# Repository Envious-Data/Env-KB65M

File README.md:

# Env-KB65M
 A 65% Custom Mechanical utilising the raspberry pi pico.
  
### About
A compact 65% design featuring ISO and ANSI layout support as well as a triple split spacebar. I designed this on a whim so its design can be considered somewhat quirky.

### Firmware
If you need a pre-built QMK firmware for this keyboard you can find it [here](https://raw.githubusercontent.com/Envious-Data/EnvKB-QMK/main/_PREBUILTFIRMWARES/enviousdesign_65m_default.uf2)
and [here](https://raw.githubusercontent.com/Envious-Data/EnvKB-QMK/main/_PREBUILTFIRMWARES/enviousdesign_65m_via.uf2)

### how to flash
- hold BOOTSEL button while plugging in USB
- A USB Drive will show up, drag and drop the UF2 file linked above into the Drive
- Done!

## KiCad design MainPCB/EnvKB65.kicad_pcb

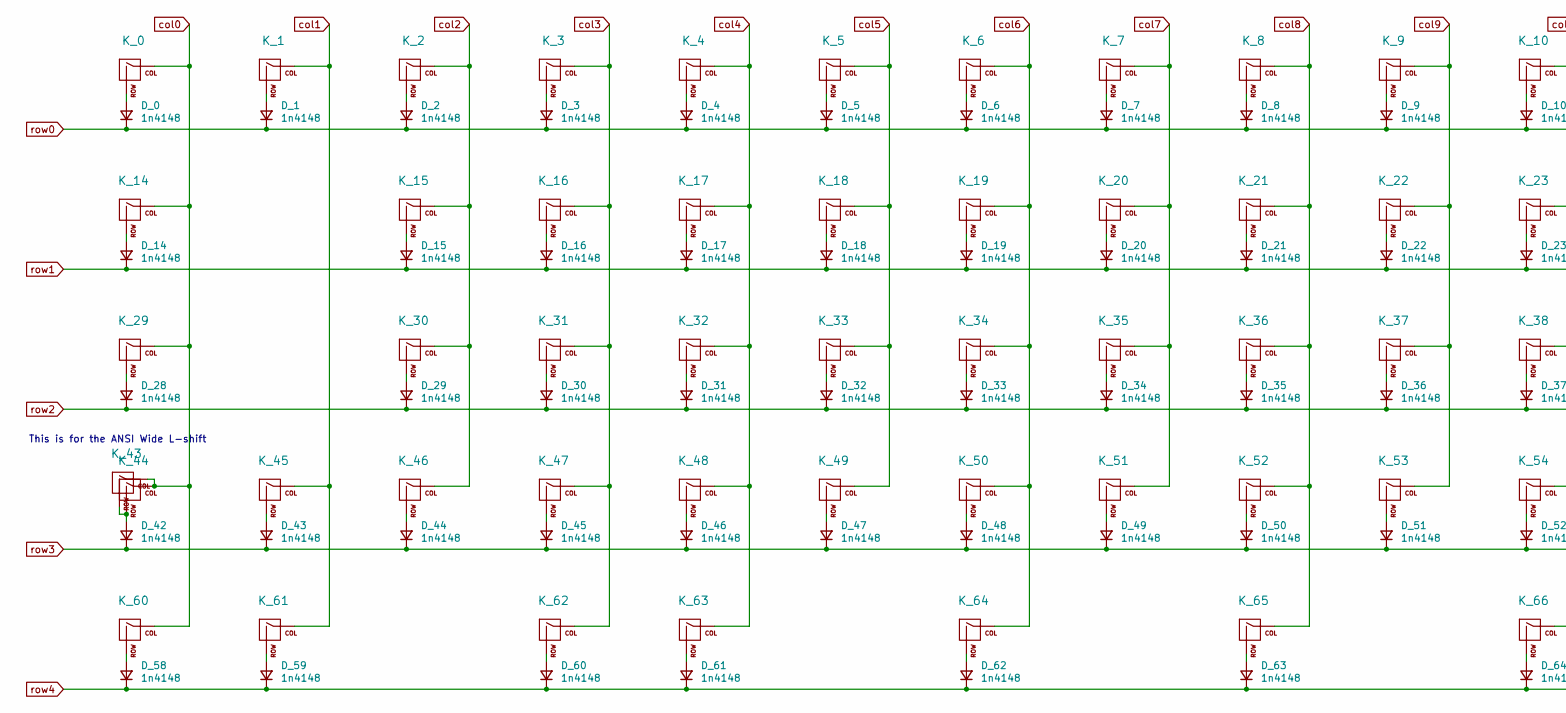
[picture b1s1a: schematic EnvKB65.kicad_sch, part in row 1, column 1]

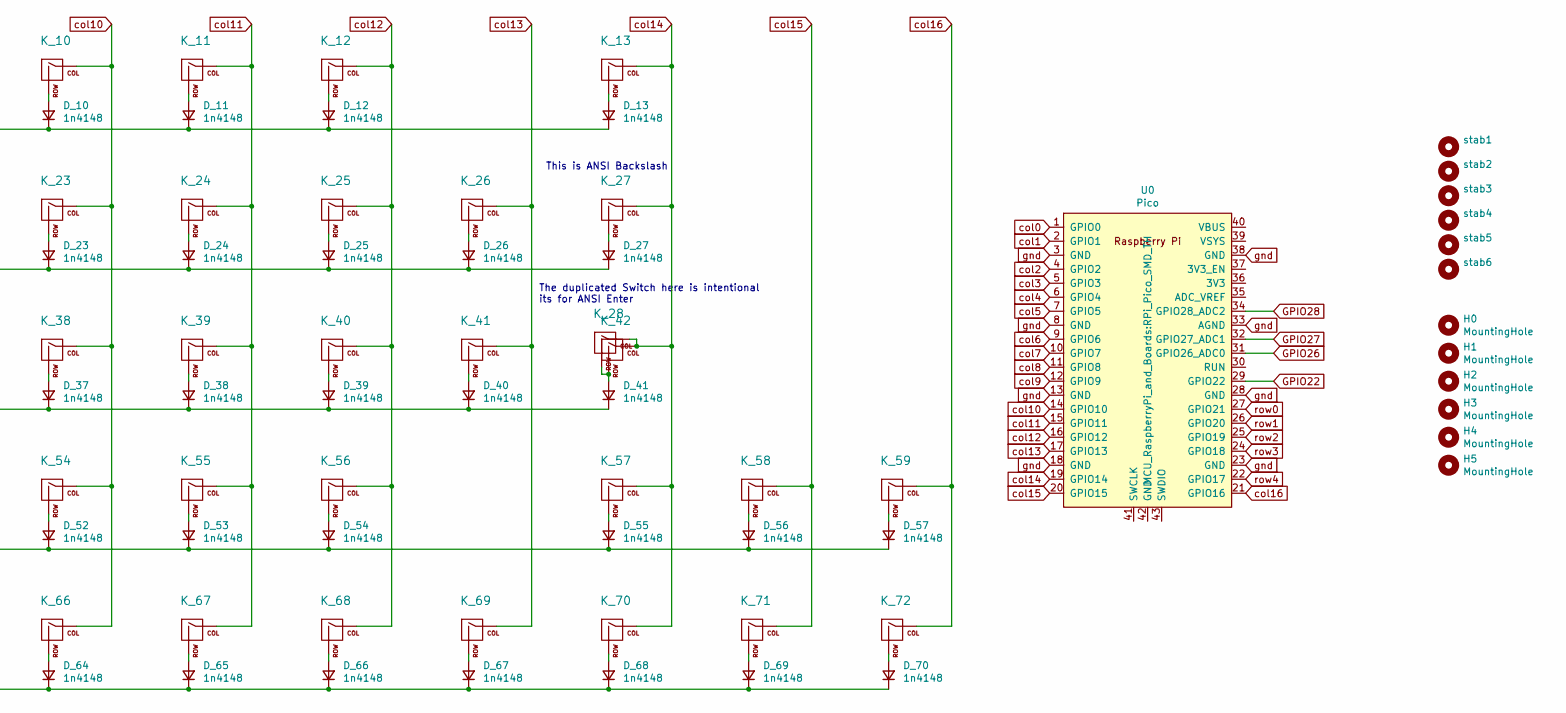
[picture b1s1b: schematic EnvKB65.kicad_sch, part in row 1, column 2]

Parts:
D_0, D_1, D_2, D_3, D_4, D_5, D_6, D_7, D_8, D_9, D_10, D_11, D_12, D_13, D_14, D_15, D_16, D_17, D_18, D_19, D_20, D_21, D_22, D_23, D_24, D_25, D_26, D_27, D_28, D_29, D_30, D_31, D_32, D_33, D_34, D_35, D_36, D_37, D_38, D_39, D_40, D_41, D_42, D_43, D_44, D_45, D_46, D_47, D_48, D_49, D_50, D_51, D_52, D_53, D_54, D_55, D_56, D_57, D_58, D_59, D_60, D_61, D_62, D_63, D_64, D_65, D_66, D_67, D_68, D_69, D_70: 1n4148; D_SOD-123
H0, H1, H2, H3, H4, H5: MountingHole; MountingHole_4.3mm_M4
K_0, K_1, K_2, K_3, K_4, K_5, K_6, K_7, K_8, K_9, K_10, K_11, K_12, K_13, K_14, K_15, K_16, K_17, K_18, K_19, K_20, K_21, K_22, K_23, K_24, K_25, K_26, K_27, K_28, K_29, K_30, K_31, K_32, K_33, K_34, K_35, K_36, K_37, K_38, K_39, K_40, K_41, K_42, K_43, K_44, K_45, K_46, K_47, K_48, K_49, K_50, K_51, K_52, K_53, K_54, K_55, K_56, K_57, K_58, K_59, K_60, K_61, K_62, K_63, K_64, K_65, K_66, K_67, K_68, K_69, K_70, K_71, K_72: MX Switch; MXOnly-1U-NoLED
U0: Pico; RPi_Pico_SMD_TH
stab1, stab2, stab3, stab4, stab5, stab6: Stabilizer; Stabilizer_Cherry_MX_2u

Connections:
GPIO22: U0.29 (GPIO22)
GPIO26: U0.31 (GPIO26_ADC0)
GPIO27: U0.32 (GPIO27_ADC1)
GPIO28: U0.34 (GPIO28_ADC2)
unnamed: D_0.2 (A), K_0.2 (ROW)
unnamed: D_1.2 (A), K_1.2 (ROW)
unnamed: D_2.2 (A), K_2.2 (ROW)
unnamed: D_3.2 (A), K_3.2 (ROW)
unnamed: D_4.2 (A), K_4.2 (ROW)
unnamed: D_5.2 (A), K_5.2 (ROW)
unnamed: D_6.2 (A), K_6.2 (ROW)
unnamed: D_7.2 (A), K_7.2 (ROW)
unnamed: D_8.2 (A), K_8.2 (ROW)
unnamed: D_9.2 (A), K_9.2 (ROW)
unnamed: D_10.2 (A), K_10.2 (ROW)
unnamed: D_11.2 (A), K_11.2 (ROW)
unnamed: D_12.2 (A), K_12.2 (ROW)
unnamed: D_13.2 (A), K_13.2 (ROW)
unnamed: D_14.2 (A), K_14.2 (ROW)
unnamed: D_15.2 (A), K_15.2 (ROW)
unnamed: D_16.2 (A), K_16.2 (ROW)
unnamed: D_17.2 (A), K_17.2 (ROW)
unnamed: D_18.2 (A), K_18.2 (ROW)
unnamed: D_19.2 (A), K_19.2 (ROW)
unnamed: D_20.2 (A), K_20.2 (ROW)
unnamed: D_21.2 (A), K_21.2 (ROW)
unnamed: D_22.2 (A), K_22.2 (ROW)
unnamed: D_23.2 (A), K_23.2 (ROW)
unnamed: D_24.2 (A), K_24.2 (ROW)
unnamed: D_25.2 (A), K_25.2 (ROW)
unnamed: D_26.2 (A), K_26.2 (ROW)
unnamed: D_27.2 (A), K_27.2 (ROW)
unnamed: D_28.2 (A), K_29.2 (ROW)
unnamed: D_29.2 (A), K_30.2 (ROW)
unnamed: D_30.2 (A), K_31.2 (ROW)
unnamed: D_31.2 (A), K_32.2 (ROW)
unnamed: D_32.2 (A), K_33.2 (ROW)
unnamed: D_33.2 (A), K_34.2 (ROW)
unnamed: D_34.2 (A), K_35.2 (ROW)
unnamed: D_35.2 (A), K_36.2 (ROW)
unnamed: D_36.2 (A), K_37.2 (ROW)
unnamed: D_37.2 (A), K_38.2 (ROW)
unnamed: D_38.2 (A), K_39.2 (ROW)
unnamed: D_39.2 (A), K_40.2 (ROW)
unnamed: D_40.2 (A), K_41.2 (ROW)
unnamed: D_41.2 (A), K_28.2 (ROW), K_42.2 (ROW)
unnamed: D_42.2 (A), K_43.2 (ROW), K_44.2 (ROW)
unnamed: D_43.2 (A), K_45.2 (ROW)
unnamed: D_44.2 (A), K_46.2 (ROW)
unnamed: D_45.2 (A), K_47.2 (ROW)
unnamed: D_46.2 (A), K_48.2 (ROW)
unnamed: D_47.2 (A), K_49.2 (ROW)
unnamed: D_48.2 (A), K_50.2 (ROW)
unnamed: D_49.2 (A), K_51.2 (ROW)
unnamed: D_50.2 (A), K_52.2 (ROW)
unnamed: D_51.2 (A), K_53.2 (ROW)
unnamed: D_52.2 (A), K_54.2 (ROW)
unnamed: D_53.2 (A), K_55.2 (ROW)
unnamed: D_54.2 (A), K_56.2 (ROW)
unnamed: D_55.2 (A), K_57.2 (ROW)
unnamed: D_56.2 (A), K_58.2 (ROW)
unnamed: D_57.2 (A), K_59.2 (ROW)
unnamed: D_58.2 (A), K_60.2 (ROW)
unnamed: D_59.2 (A), K_61.2 (ROW)
unnamed: D_60.2 (A), K_62.2 (ROW)
unnamed: D_61.2 (A), K_63.2 (ROW)
unnamed: D_62.2 (A), K_64.2 (ROW)
unnamed: D_63.2 (A), K_65.2 (ROW)
unnamed: D_64.2 (A), K_66.2 (ROW)
unnamed: D_65.2 (A), K_67.2 (ROW)
unnamed: D_66.2 (A), K_68.2 (ROW)
unnamed: D_67.2 (A), K_69.2 (ROW)
unnamed: D_68.2 (A), K_70.2 (ROW)
unnamed: D_69.2 (A), K_71.2 (ROW)
unnamed: D_70.2 (A), K_72.2 (ROW)
col0: K_0.1 (COL), K_14.1 (COL), K_29.1 (COL), K_43.1 (COL), K_44.1 (COL), K_60.1 (COL), U0.1 (GPIO0)
col1: K_1.1 (COL), K_45.1 (COL), K_61.1 (COL), U0.2 (GPIO1)
col2: K_2.1 (COL), K_15.1 (COL), K_30.1 (COL), K_46.1 (COL), U0.4 (GPIO2)
col3: K_3.1 (COL), K_16.1 (COL), K_31.1 (COL), K_47.1 (COL), K_62.1 (COL), U0.5 (GPIO3)
col4: K_4.1 (COL), K_17.1 (COL), K_32.1 (COL), K_48.1 (COL), K_63.1 (COL), U0.6 (GPIO4)
col5: K_5.1 (COL), K_18.1 (COL), K_33.1 (COL), K_49.1 (COL), U0.7 (GPIO5)
col6: K_6.1 (COL), K_19.1 (COL), K_34.1 (COL), K_50.1 (COL), K_64.1 (COL), U0.9 (GPIO6)
col7: K_7.1 (COL), K_20.1 (COL), K_35.1 (COL), K_51.1 (COL), U0.10 (GPIO7)
col8: K_8.1 (COL), K_21.1 (COL), K_36.1 (COL), K_52.1 (COL), K_65.1 (COL), U0.11 (GPIO8)
col9: K_9.1 (COL), K_22.1 (COL), K_37.1 (COL), K_53.1 (COL), U0.12 (GPIO9)
col10: K_10.1 (COL), K_23.1 (COL), K_38.1 (COL), K_54.1 (COL), K_66.1 (COL), U0.14 (GPIO10)
col11: K_11.1 (COL), K_24.1 (COL), K_39.1 (COL), K_55.1 (COL), K_67.1 (COL), U0.15 (GPIO11)
col12: K_12.1 (COL), K_25.1 (COL), K_40.1 (COL), K_56.1 (COL), K_68.1 (COL), U0.16 (GPIO12)
col13: K_26.1 (COL), K_41.1 (COL), K_69.1 (COL), U0.17 (GPIO13)
col14: K_13.1 (COL), K_27.1 (COL), K_28.1 (COL), K_42.1 (COL), K_57.1 (COL), K_70.1 (COL), U0.19 (GPIO14)
col15: K_58.1 (COL), K_71.1 (COL), U0.20 (GPIO15)
col16: K_59.1 (COL), K_72.1 (COL), U0.21 (GPIO16)
gnd: U0.3 (GND), U0.8 (GND), U0.13 (GND), U0.18 (GND), U0.23 (GND), U0.28 (GND), U0.33 (AGND), U0.38 (GND)
row0: D_0.1 (K), D_1.1 (K), D_2.1 (K), D_3.1 (K), D_4.1 (K), D_5.1 (K), D_6.1 (K), D_7.1 (K), D_8.1 (K), D_9.1 (K), D_10.1 (K), D_11.1 (K), D_12.1 (K), D_13.1 (K), U0.27 (GPIO21)
row1: D_14.1 (K), D_15.1 (K), D_16.1 (K), D_17.1 (K), D_18.1 (K), D_19.1 (K), D_20.1 (K), D_21.1 (K), D_22.1 (K), D_23.1 (K), D_24.1 (K), D_25.1 (K), D_26.1 (K), D_27.1 (K), U0.26 (GPIO20)
row2: D_28.1 (K), D_29.1 (K), D_30.1 (K), D_31.1 (K), D_32.1 (K), D_33.1 (K), D_34.1 (K), D_35.1 (K), D_36.1 (K), D_37.1 (K), D_38.1 (K), D_39.1 (K), D_40.1 (K), D_41.1 (K), U0.25 (GPIO19)
row3: D_42.1 (K), D_43.1 (K), D_44.1 (K), D_45.1 (K), D_46.1 (K), D_47.1 (K), D_48.1 (K), D_49.1 (K), D_50.1 (K), D_51.1 (K), D_52.1 (K), D_53.1 (K), D_54.1 (K), D_55.1 (K), D_56.1 (K), D_57.1 (K), U0.24 (GPIO18)
row4: D_58.1 (K), D_59.1 (K), D_60.1 (K), D_61.1 (K), D_62.1 (K), D_63.1 (K), D_64.1 (K), D_65.1 (K), D_66.1 (K), D_67.1 (K), D_68.1 (K), D_69.1 (K), D_70.1 (K), U0.22 (GPIO17)

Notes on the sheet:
The duplicated Switch here is intentional its for ANSI Enter
This is ANSI Backslash
This is for the ANSI Wide L-shift

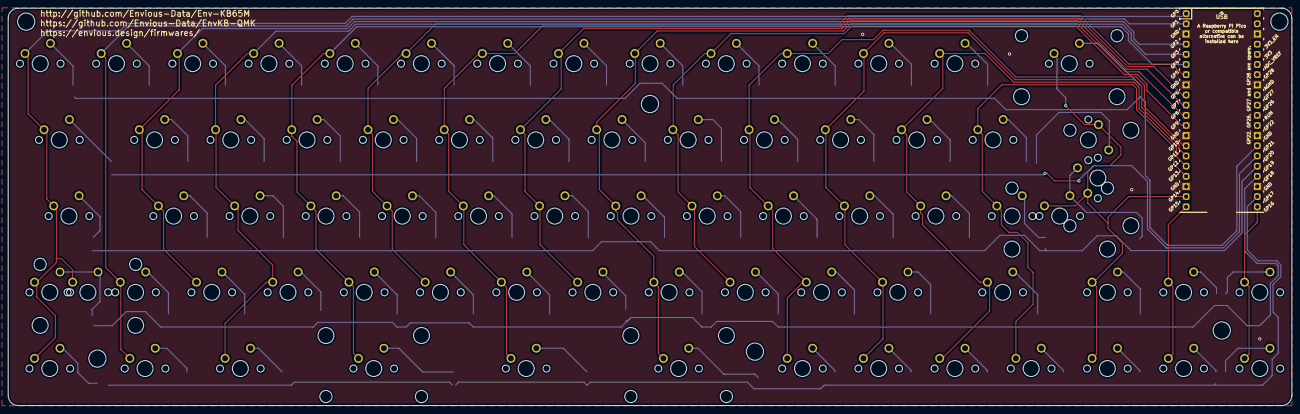
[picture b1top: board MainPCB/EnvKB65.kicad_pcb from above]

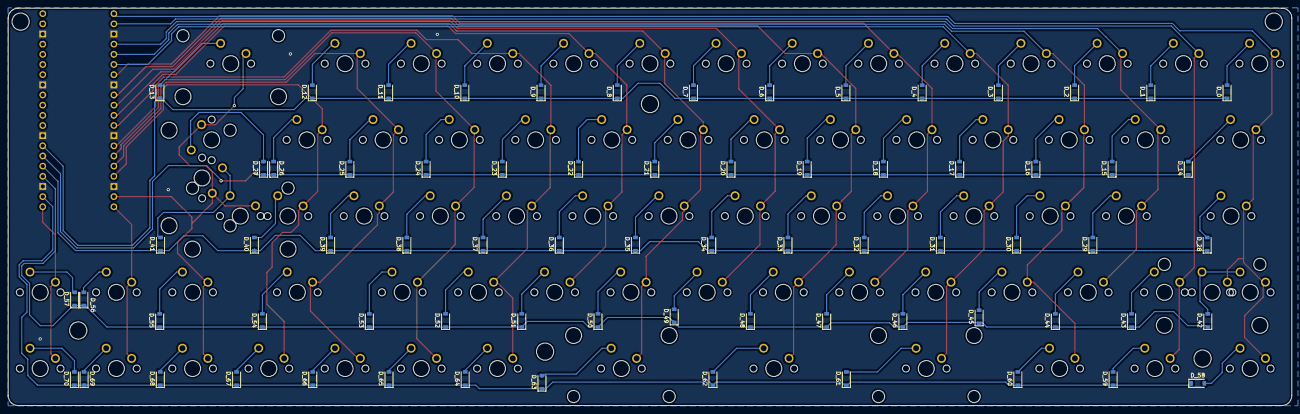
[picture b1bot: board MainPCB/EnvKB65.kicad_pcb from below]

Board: 2 copper layers, 320.8 x 99.3 mm, 157 parts (71 on the bottom side), 94 nets.

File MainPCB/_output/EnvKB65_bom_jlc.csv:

"Comment","Designator","Footprint","LCSC Part #"
"Diode SOD-323","D_0,D_1,D_2,D_3,D_4,D_5,D_6,D_7,D_8,D_9,D_10,D_11,D_12,D_13,D_14,D_15,D_16,D_17,D_18,D_19,D_20,D_21,D_22,D_23,D_24,D_25,D_26,D_28,D_29,D_30,D_31,D_32,D_33,D_34,D_35,D_36,D_37,D_38,D_39,D_40,D_41,D_42,D_43,D_44,D_45,D_46,D_47,D_48,D_49,D_50,D_51,D_52,D_53,D_54,D_55,D_56,D_57,D_58,D_59,D_60,D_61,D_62,D_63,D_64,D_65,D_66,D_67,D_68,D_69,D_70,D_27","D_SOD-323_HandSoldering","C727111"
"MountingHole","H0,H1,H2,H3,H4,H5","MountingHole_2.2mm_M2_Pad","no_part_number"
"KEYSW","K_0,K_1,K_2,K_3,K_4,K_5,K_6,K_7,K_8,K_9,K_10,K_11,K_12,K_15,K_16,K_17,K_18,K_19,K_20,K_21,K_22,K_23,K_24,K_25,K_26,K_30,K_31,K_32,K_33,K_34,K_35,K_36,K_37,K_38,K_39,K_40,K_41,K_45,K_46,K_47,K_48,K_49,K_50,K_51,K_52,K_53,K_54,K_55,K_57,K_58,K_59,K_66,K_67,K_68,K_69,K_70,K_71,K_72","MXOnly-1U-NoLED","no_part_number"
"KEYSW","K_13","MXOnly-2U-NoLED","no_part_number"
"KEYSW","K_14,K_27","MXOnly-1.5U-NoLED","no_part_number"
"KEYSW","K_28,K_43","MXOnly-2.25U-NoLED","no_part_number"
"KEYSW","K_29,K_56,K_64","MXOnly-1.75U-NoLED","no_part_number"
"KEYSW","K_42","MXOnly-ISO-ROTATED-ReversedStabilizers-NoLED","no_part_number"
"KEYSW","K_44,K_60,K_61,K_62","MXOnly-1.25U-NoLED","no_part_number"
"KEYSW","K_63,K_65","MXOnly-2.25U-ReversedStabilizers-NoLED","no_part_number"
"Pico","U0","RPi_Pico_SMD_TH","no_part_number"

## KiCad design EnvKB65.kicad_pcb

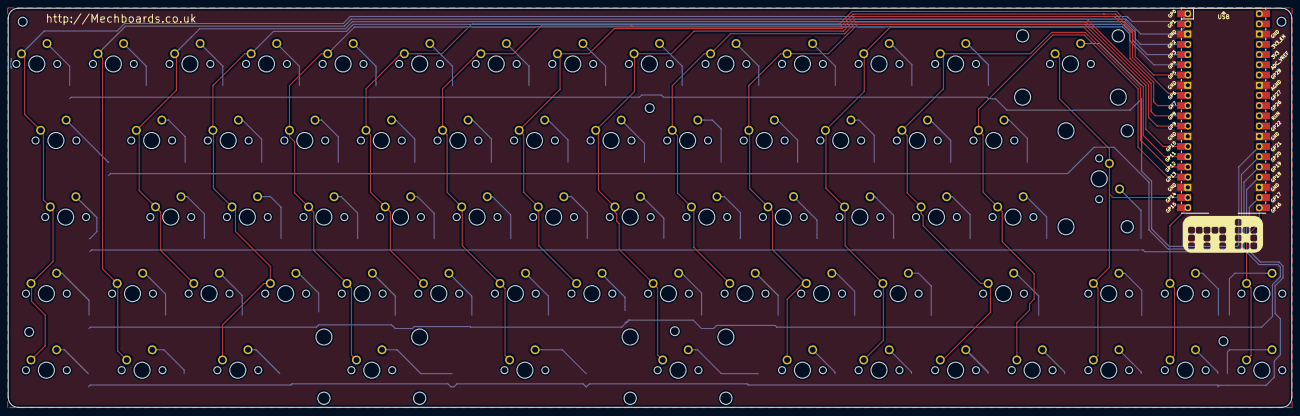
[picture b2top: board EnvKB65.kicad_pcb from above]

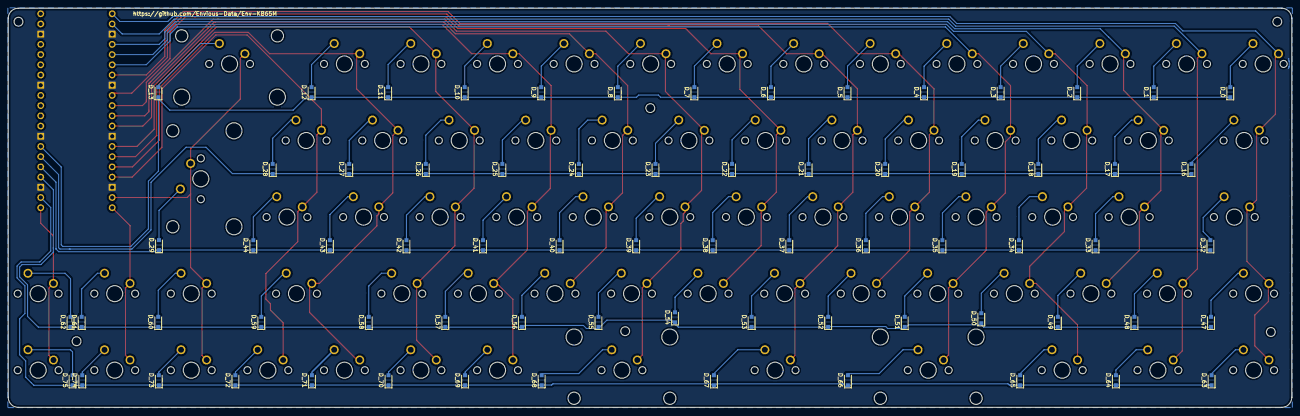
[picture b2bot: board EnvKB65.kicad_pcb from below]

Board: 2 copper layers, 319.4 x 99.3 mm, 148 parts (70 on the bottom side), 93 nets.

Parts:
D_0, D_1, D_2, D_3, D_4, D_5, D_6, D_7, D_8, D_9, D_10, D_11, D_12, D_13, D_16, D_17, D_18, D_19, D_20, D_21, D_22, D_23, D_24, D_25, D_26, D_27, D_28, D_29, D_32, D_33, D_34, D_35, D_36, D_37, D_38, D_39, D_40, D_41, D_42, D_43, D_44, D_47, D_48, D_49, D_50, D_51, D_52, D_53, D_54, D_55, D_56, D_57, D_58, D_59, D_60, D_61, D_62, D_63, D_64, D_65, D_66, D_67, D_68, D_69, D_70, D_71, D_72, D_73, D_74, D_75: D; D_SOD-323_HandSoldering
H1, H2, H3, H4, H5, H6: MountingHole; MountingHole_2.2mm_M2
K_0, K_1, K_2, K_3, K_4, K_5, K_6, K_7, K_8, K_9, K_10, K_11, K_12, K_17, K_18, K_19, K_20, K_21, K_22, K_23, K_24, K_25, K_26, K_27, K_28, K_33, K_34, K_35, K_36, K_37, K_38, K_39, K_40, K_41, K_42, K_43, K_44, K_48, K_49, K_50, K_51, K_52, K_53, K_54, K_55, K_56, K_57, K_58, K_60, K_61, K_62, K_69, K_70, K_71, K_72, K_73, K_74, K_75: KEYSW; MXOnly-1U-NoLED
K_13: KEYSW; MXOnly-2U-NoLED
K_16: KEYSW; MXOnly-1.5U-NoLED
K_29: KEYSW; MXOnly-ISO-ROTATED-ReversedStabilizers-NoLED
K_32, K_59, K_67: KEYSW; MXOnly-1.75U-NoLED
K_47, K_63, K_64, K_65: KEYSW; MXOnly-1.25U-NoLED
K_66, K_68: KEYSW; MXOnly-2.25U-ReversedStabilizers-NoLED
Ref**: Val**; mechboardsLOGO_20mm
U1: Pico; RPi_Pico_SMD_TH

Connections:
unnamed: D_0.2, K_0.2
unnamed: D_1.2, K_1.2
unnamed: D_2.2, K_2.2
unnamed: D_3.2, K_3.2
unnamed: D_4.2, K_4.2
unnamed: D_5.2, K_5.2
unnamed: D_6.2, K_6.2
unnamed: D_7.2, K_7.2
unnamed: D_8.2, K_8.2
unnamed: D_9.2, K_9.2
unnamed: D_10.2, K_10.2
unnamed: D_11.2, K_11.2
unnamed: D_12.2, K_12.2
unnamed: D_13.2, K_13.2
unnamed: D_16.2, K_16.2
unnamed: D_17.2, K_17.2
unnamed: D_18.2, K_18.2
unnamed: D_19.2, K_19.2
unnamed: D_20.2, K_20.2
unnamed: D_21.2, K_21.2
unnamed: D_22.2, K_22.2
unnamed: D_23.2, K_23.2
unnamed: D_24.2, K_24.2
unnamed: D_25.2, K_25.2
unnamed: D_26.2, K_26.2
unnamed: D_27.2, K_27.2
unnamed: D_28.2, K_28.2
unnamed: D_29.2, K_29.2
unnamed: D_32.2, K_32.2
unnamed: D_33.2, K_33.2
unnamed: D_34.2, K_34.2
unnamed: D_35.2, K_35.2
unnamed: D_36.2, K_36.2
unnamed: D_37.2, K_37.2
unnamed: D_38.2, K_38.2
unnamed: D_39.2, K_39.2
unnamed: D_40.2, K_40.2
unnamed: D_41.2, K_41.2
unnamed: D_42.2, K_42.2
unnamed: D_43.2, K_43.2
unnamed: D_44.2, K_44.2
unnamed: D_47.2, K_47.2
unnamed: D_48.2, K_48.2
unnamed: D_49.2, K_49.2
unnamed: D_50.2, K_50.2
unnamed: D_51.2, K_51.2
unnamed: D_52.2, K_52.2
unnamed: D_53.2, K_53.2
unnamed: D_54.2, K_54.2
unnamed: D_55.2, K_55.2
unnamed: D_56.2, K_56.2
unnamed: D_57.2, K_57.2
unnamed: D_58.2, K_58.2
unnamed: D_59.2, K_59.2
unnamed: D_60.2, K_60.2
unnamed: D_61.2, K_61.2
unnamed: D_62.2, K_62.2
unnamed: D_63.2, K_63.2
unnamed: D_64.2, K_64.2
unnamed: D_65.2, K_65.2
unnamed: D_66.2, K_66.2
unnamed: D_67.2, K_67.2
unnamed: D_68.2, K_68.2
unnamed: D_69.2, K_69.2
unnamed: D_70.2, K_70.2
unnamed: D_71.2, K_71.2
unnamed: D_72.2, K_72.2
unnamed: D_73.2, K_73.2
unnamed: D_74.2, K_74.2
unnamed: D_75.2, K_75.2
col0: K_0.1, K_16.1, K_32.1, K_47.1, K_63.1, U1.1
col1: K_1.1, K_48.1, K_64.1, U1.2
col2: K_2.1, K_17.1, K_33.1, K_49.1, U1.4
col3: K_3.1, K_18.1, K_34.1, K_50.1, K_65.1, U1.5
col4: K_4.1, K_19.1, K_35.1, K_51.1, K_66.1, U1.6
col5: K_5.1, K_20.1, K_36.1, K_52.1, U1.7
col6: K_6.1, K_21.1, K_37.1, K_53.1, K_67.1, U1.9
col7: K_7.1, K_22.1, K_38.1, K_54.1, U1.10
col8: K_8.1, K_23.1, K_39.1, K_55.1, K_68.1, U1.11
col9: K_9.1, K_24.1, K_40.1, K_56.1, U1.12
col10: K_10.1, K_25.1, K_41.1, K_57.1, K_69.1, U1.14
col11: K_11.1, K_26.1, K_42.1, K_58.1, K_70.1, U1.15
col12: K_12.1, K_27.1, K_43.1, K_59.1, K_71.1, U1.16
col13: K_28.1, K_44.1, K_72.1, U1.17
col14: K_13.1, K_29.1, K_60.1, K_73.1, U1.19
col15: K_61.1, K_74.1, U1.20
col16: K_62.1, K_75.1, U1.21
gnd: U1.3, U1.8, U1.13, U1.18, U1.23, U1.28, U1.33, U1.38
row0: D_0.1, D_1.1, D_2.1, D_3.1, D_4.1, D_5.1, D_6.1, D_7.1, D_8.1, D_9.1, D_10.1, D_11.1, D_12.1, D_13.1, U1.27
row1: D_16.1, D_17.1, D_18.1, D_19.1, D_20.1, D_21.1, D_22.1, D_23.1, D_24.1, D_25.1, D_26.1, D_27.1, D_28.1, U1.26
row2: D_29.1, D_32.1, D_33.1, D_34.1, D_35.1, D_36.1, D_37.1, D_38.1, D_39.1, D_40.1, D_41.1, D_42.1, D_43.1, D_44.1, U1.25
row3: D_47.1, D_48.1, D_49.1, D_50.1, D_51.1, D_52.1, D_53.1, D_54.1, D_55.1, D_56.1, D_57.1, D_58.1, D_59.1, D_60.1, D_61.1, D_62.1, U1.24
row4: D_63.1, D_64.1, D_65.1, D_66.1, D_67.1, D_68.1, D_69.1, D_70.1, D_71.1, D_72.1, D_73.1, D_74.1, D_75.1, U1.22

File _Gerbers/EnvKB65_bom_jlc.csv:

"Comment","Designator","Footprint","LCSC Part #"
"Diode SOD-323","D_0,D_1,D_2,D_3,D_4,D_5,D_6,D_7,D_8,D_9,D_10,D_11,D_12,D_13,D_14,D_16,D_17,D_18,D_19,D_20,D_21,D_22,D_23,D_24,D_25,D_26,D_27,D_28,D_30,D_32,D_33,D_34,D_35,D_36,D_37,D_38,D_39,D_40,D_41,D_42,D_43,D_44,D_29,D_45,D_47,D_48,D_49,D_50,D_51,D_52,D_53,D_54,D_55,D_56,D_57,D_58,D_59,D_60,D_61,D_62,D_63,D_64,D_65,D_66,D_67,D_68,D_69,D_70,D_71,D_72,D_73,D_74,D_75,D_46,D_31,D_15","D_SOD-323_HandSoldering","C727111"
"MountingHole","H1,H2,H3,H4,H5,H6","MountingHole_2.2mm_M2","no_part_number"
"KEYSW","K_0,K_1,K_2,K_3,K_4,K_5,K_6,K_7,K_8,K_9,K_10,K_11,K_12,K_14,K_17,K_18,K_19,K_20,K_21,K_22,K_23,K_24,K_25,K_26,K_27,K_28,K_30,K_33,K_34,K_35,K_36,K_37,K_38,K_39,K_40,K_41,K_42,K_43,K_44,K_45,K_48,K_49,K_50,K_51,K_52,K_53,K_54,K_55,K_56,K_57,K_58,K_60,K_61,K_62,K_69,K_70,K_71,K_72,K_73,K_74,K_75,K_46,K_31,K_15","MXOnly-1U-NoLED","no_part_number"
"KEYSW","K_13","MXOnly-2U-NoLED","no_part_number"
"KEYSW","K_16","MXOnly-1.5U-NoLED","no_part_number"
"KEYSW","K_29","MXOnly-ISO-ROTATED-ReversedStabilizers-NoLED","no_part_number"
"KEYSW","K_32,K_59,K_67","MXOnly-1.75U-NoLED","no_part_number"
"KEYSW","K_47,K_63,K_64,K_65","MXOnly-1.25U-NoLED","no_part_number"
"KEYSW","K_66,K_68","MXOnly-2.25U-ReversedStabilizers-NoLED","no_part_number"
"Pico","U1","RPi_Pico_SMD_TH","no_part_number"

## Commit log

2021-05-16 Initial commit+1
2021-05-16 Updated Readme w/ Image
2021-05-17 slimmed design down a bit at the cost of some keys
2021-05-17 Routed Traces, Add Mounting holes and edge cuts
2021-05-17 Final Adjustments And Gerber Creation for Revision0
2021-05-17 Changed Diodes to SOD-323 and separated Position files
2021-05-17 corrected issue + made blank bottom PCB
2021-05-17 General Cleanup, board resize and correction of things + made top switch plate
2021-05-27 Swapped out mechboads logo for personal order
2021-05-27 General cleanup and testing of improved Gerber generation
2021-05-30 moved LICENSE to correct place
2021-05-31 Added ANSI support, generated Gerbers and sent to JLCPCB
2021-05-31 Embiggened the PCB to allow for 4mm edge spaces to comply with JLCPCB
2021-06-11 corrected a couple silkscreen issues and moved some traces further from some holes.
2021-06-11 Created Firmware and keymap (this is unfinished, need a 65% user to add on this)
2021-06-22 Mount hole tweak to allow for switches to seat properly with a spacer installed
2021-06-28 slightly updated keymap
2021-06-28 added escape key to keymap
2021-06-28 moved some mount holes a tiny bit and adjusted some traces for wider clearance.
2021-07-10 moved mount hole#6 up by 1mm and changed stabilizer cut out.
2021-07-29 Cleaned up a couple strange mistakes.
2021-07-29 removed redundant url.
2021-07-29 moved mount hole "H5" to the right by 40.5mm on all PCBs
2021-07-30 replaced all mount holes with versions that have pads
    I did this because the pcb can get scraped up if you take it apart a bunch of times to clean it, hopefully this mitigates that.
2021-08-04 Generated some Gerbers and added some testing graphics for now.
2021-08-14 started work on a version with an onboard atmega32u4
2021-08-15 changed my mind, I wanted the 32u version to have more switches, going to figure out if I can fit the MCU somewhere on the back of the board.
2021-08-15 finished running traces, probably need to clean up some bits and pieces.
2021-08-15 adjusted some bits to comply with DRC.
2021-08-16 a decoupling capacitor was in a bad position
2021-08-22 updated silkscreen and also made 32u switch plate.
2021-08-22 generated updated gerbers for 32u4 version
2021-08-22 started work on a RP2040 version with the same layout as the 32u4 version
2021-08-22 continued work on the RP2040 version
2021-08-22 finished off RP2040 version, needs general check overs and cleanup.
2021-08-22 moved some resistors and capacitors to account for screw hole clearance for the stabilizer holes.
2021-10-05 See List
    * removed RP2040 and atmega32u4 versions
    * updated main PCB to have larger holes
    * fixed some stuff on the main PCB and added some labels
2021-10-05 Generated Up to date gerbers.
2021-10-30 Started work on hotswap version
2021-10-30 small cleanup + worked on routing races and all
2021-10-31 fixed some trace and pad/hole conflictions and spaced some traces although not causing DRC errors.
2021-10-31 Renamed KiCad Project appropriately
2021-10-31 Generated Gerber, fixed gitignore
2021-10-31 corrected hotswap socket being cut off on the left side (PCB is slightly wider)
2021-12-04 adjusted design and fixed issues, Generated updated gerber
2021-12-04 moved gerber to correct place
2021-12-04 updated BOM and CPL
2021-12-04 added switch plate to ECO2
2021-12-05 Generated updated Gerber
2022-01-16 made some fixes to silkscreen and a general check over to prepare for ordering.
2022-04-14 some adjustments for hotswap version
2022-04-15 some small fixes
2022-05-02 attempted fix for hotswap iso/ansi compatibility
2022-05-06 smol checkthrough and gerber generation of 65 hotswap
2022-05-10 various corrections and updated gerbers, bom, cpls
2022-05-17 updated gerbers, BOM and CPL
2022-05-28 updated switch plate to be PCB mount only.
2022-05-28 Removed Mechboards branding as there is now a mechboards fork
2022-05-28 Roundified Tracks because why not
2022-05-28 added i2c header for oled
2022-05-30 some tweaks to traces here and there to ensure decent clearance
2022-06-01 updated gerber
2022-06-02 some small correction to a couple traces
2022-06-12 swapped mount holes to solderable inserts and fixed some potential clearance issues
2022-06-12 larger holes for aliexpress smd mounts
2022-06-18 swapped mount holes back and generated updated gerbers and etc
2022-06-27 swapped diodes to larger footprint and corrected DRC errors
2022-07-04 added GND plane fill, generated updated gerber
2022-11-05 created choc V2 variant with plate on user layer
2022-12-01 updated KLE doc
2023-02-10 added HOTSWAP version to gerber folder
2023-04-24 fixed small issue with up arrow key
2023-09-24 small repo cleanup + updated readme
